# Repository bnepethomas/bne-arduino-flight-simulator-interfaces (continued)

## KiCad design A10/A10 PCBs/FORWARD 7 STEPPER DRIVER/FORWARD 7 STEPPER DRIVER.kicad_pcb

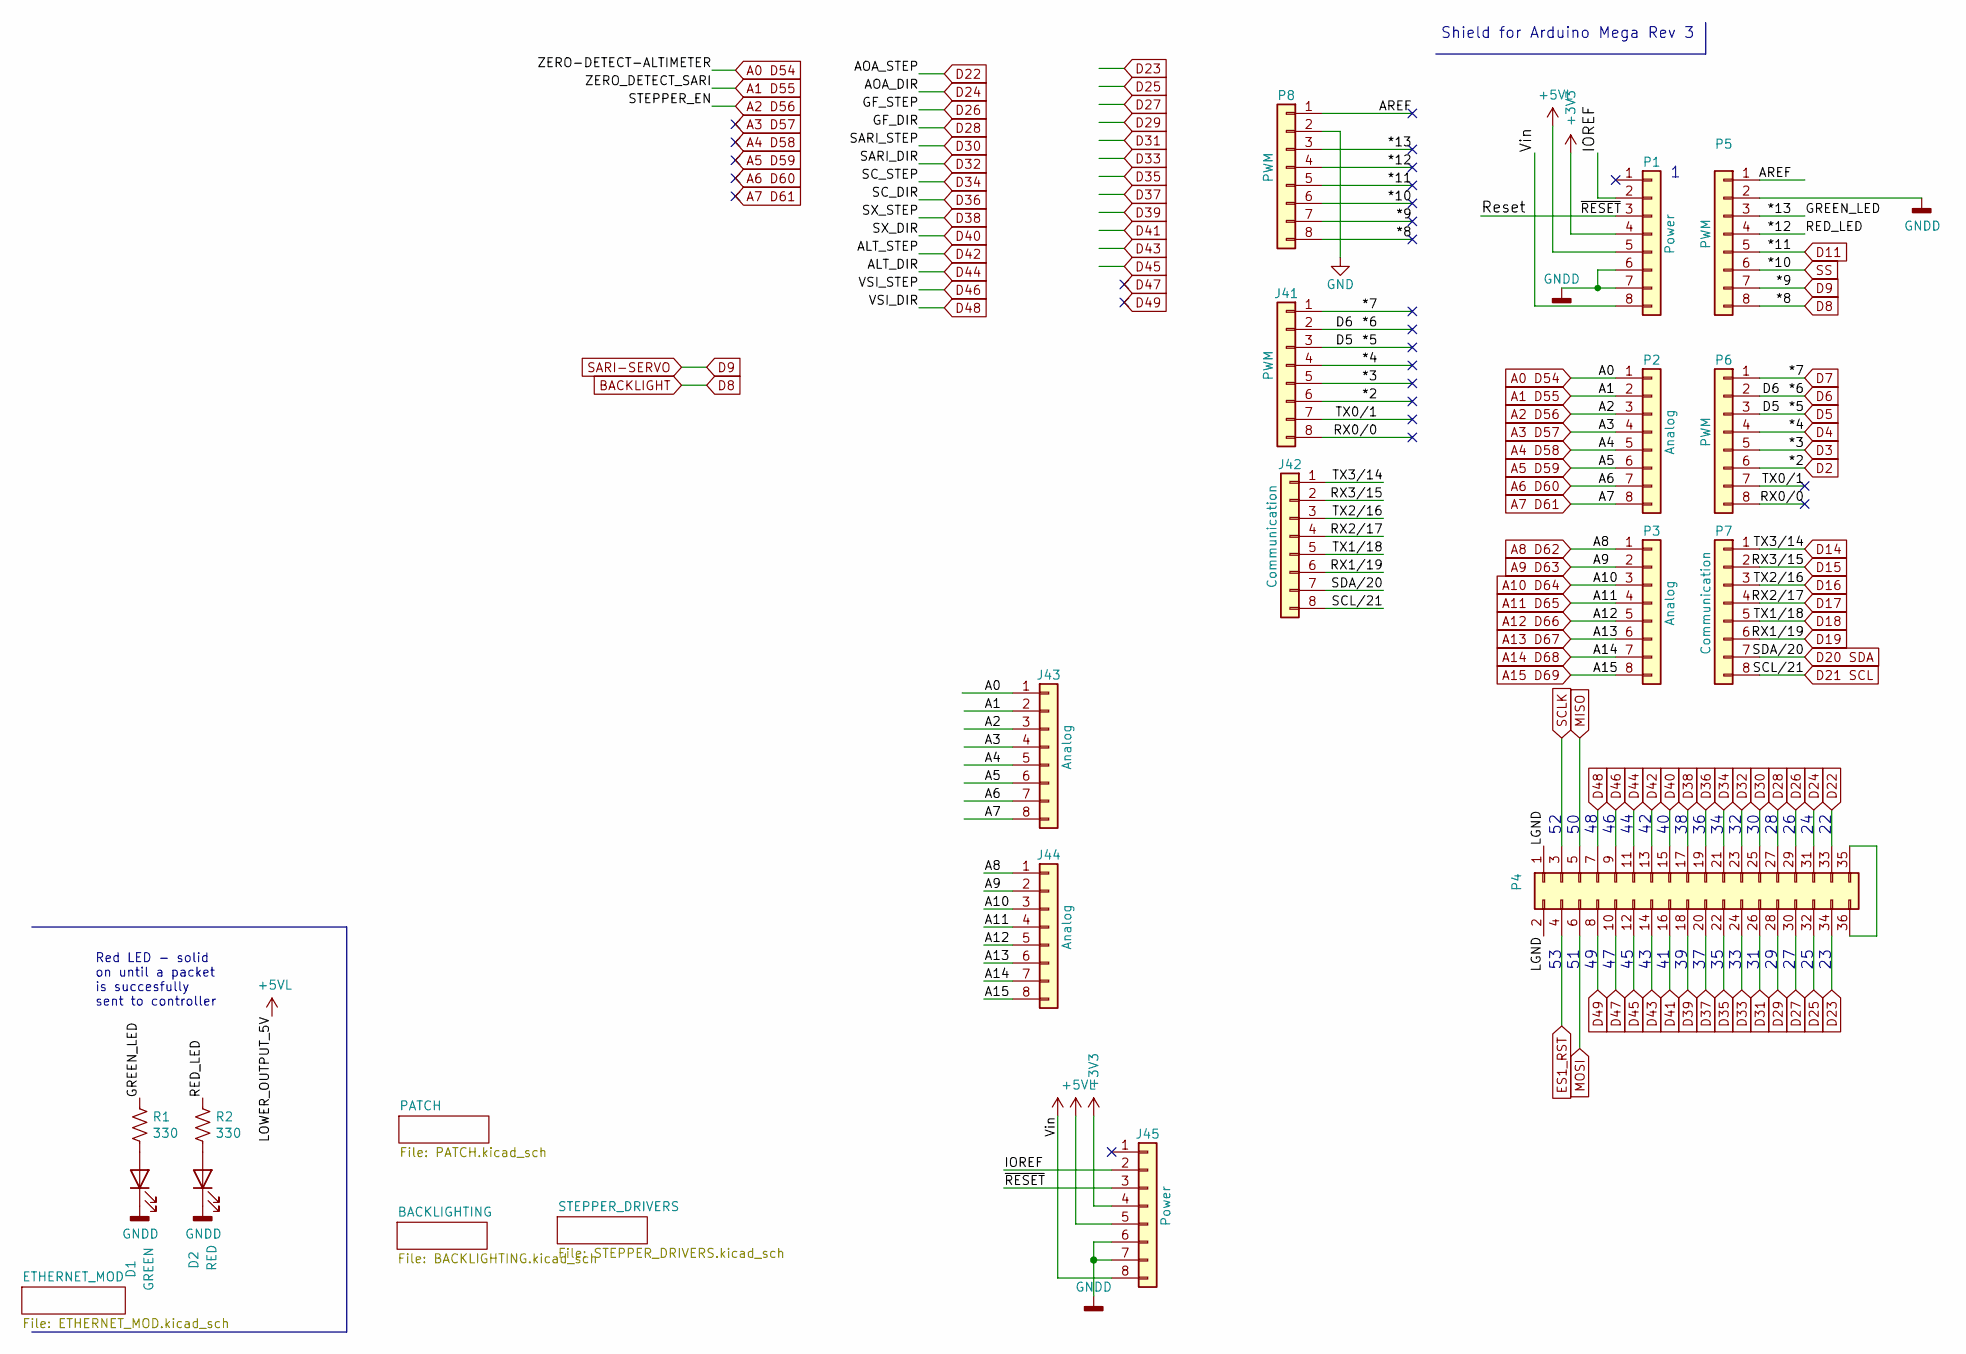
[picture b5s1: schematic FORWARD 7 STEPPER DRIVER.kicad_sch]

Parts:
D1: GREEN; LED_D3.0mm
D2: RED; LED_D3.0mm
J41: PWM; PinSocket_1x08_P2.54mm_Vertical
J42: Communication; PinSocket_1x08_P2.54mm_Vertical
J43, J44: Analog; PinSocket_1x08_P2.54mm_Vertical
J45: Power; PinSocket_1x08_P2.54mm_Vertical
P1: Power; Socket_Strip_Arduino_1x08
P2, P3: Analog; Socket_Strip_Arduino_1x08
P4: Digital; Socket_Strip_Arduino_2x18
P5, P6, P8: PWM; Socket_Strip_Arduino_1x08
P7: Communication; Socket_Strip_Arduino_1x08
R1: 330; R_Axial_DIN0204_L3.6mm_D1.6mm_P2.54mm_Vertical
R2: 330; PT_R_Axial_DIN0204_L3.6mm_D1.6mm_P2.54mm_Vertical

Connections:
+3V3: J45.4, P1.4; also elsewhere on the board
+5VL: J45.5, P1.5; also elsewhere on the board
/*12: P5.4, P8.4, R2.1
/*13: P5.3, P8.3, R1.1
/AREF: P5.1, P8.1
/IOREF: J45.2, P1.2
/LGND: P4.1, P4.2
/RX0/0: J41.8, P6.8
/Reset: J45.3, P1.3
/TX0/1: J41.7, P6.7
A0 D54: J43.1, P2.1; also elsewhere on the board
A1 D55: J43.2, P2.2; also elsewhere on the board
A2 D56: J43.3, P2.3; also elsewhere on the board
A3 D57: J43.4, P2.4
A4 D58: J43.5, P2.5
A5 D59: J43.6, P2.6
A6 D60: J43.7, P2.7
A7 D61: J43.8, P2.8
A8 D62: J44.1, P3.1
A9 D63: J44.2, P3.2
A10 D64: J44.3, P3.3
A11 D65: J44.4, P3.4
A12 D66: J44.5, P3.5
A13 D67: J44.6, P3.6
A14 D68: J44.7, P3.7
A15 D69: J44.8, P3.8
BACKLIGHT: P5.8, P8.8; also elsewhere on the board
D2: J41.6, P6.6
D3: J41.5, P6.5
D4: J41.4, P6.4
D5: J41.3, P6.3
D6: J41.2, P6.2
D7: J41.1, P6.1
D9: P5.7, P8.7; also elsewhere on the board
D11: P5.5, P8.5
D14: J42.1, P7.1
D15: J42.2, P7.2
D16: J42.3, P7.3
D17: J42.4, P7.4
D18: J42.5, P7.5
D19: J42.6, P7.6
D20 SDA: J42.7, P7.7
D21 SCL: J42.8, P7.8
D22: P4.33; also elsewhere on the board
D23: P4.34
D24: P4.31; also elsewhere on the board
D25: P4.32
D26: P4.29; also elsewhere on the board
D27: P4.30
D28: P4.27; also elsewhere on the board
D29: P4.28
D30: P4.25; also elsewhere on the board
D31: P4.26
D32: P4.23; also elsewhere on the board
D33: P4.24
D34: P4.21; also elsewhere on the board
D35: P4.22
D36: P4.19; also elsewhere on the board
D37: P4.20
D38: P4.17; also elsewhere on the board
D39: P4.18
D40: P4.15; also elsewhere on the board
D41: P4.16
D42: P4.13; also elsewhere on the board
D43: P4.14
D44: P4.11; also elsewhere on the board
D45: P4.12
D46: P4.9; also elsewhere on the board
D47: P4.10
D48: P4.7; also elsewhere on the board
D49: P4.8
ES1_RST: P4.4; also elsewhere on the board
GND: D1.1 (K), D2.1 (K), J45.6, J45.7, P1.6, P1.7, P5.2, P8.2; also elsewhere on the board
MISO: P4.5; also elsewhere on the board
MOSI: P4.6; also elsewhere on the board
unnamed: D1.2 (A), R1.2
unnamed: D2.2 (A), R2.2
unnamed: P4.35, P4.36
SCLK: P4.3; also elsewhere on the board
SS: P5.6, P8.6; also elsewhere on the board
VCC: J45.8, P1.8

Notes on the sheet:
Shield for Arduino Mega Rev 3
Red LED - solid on until a packet is succesfully sent to controller

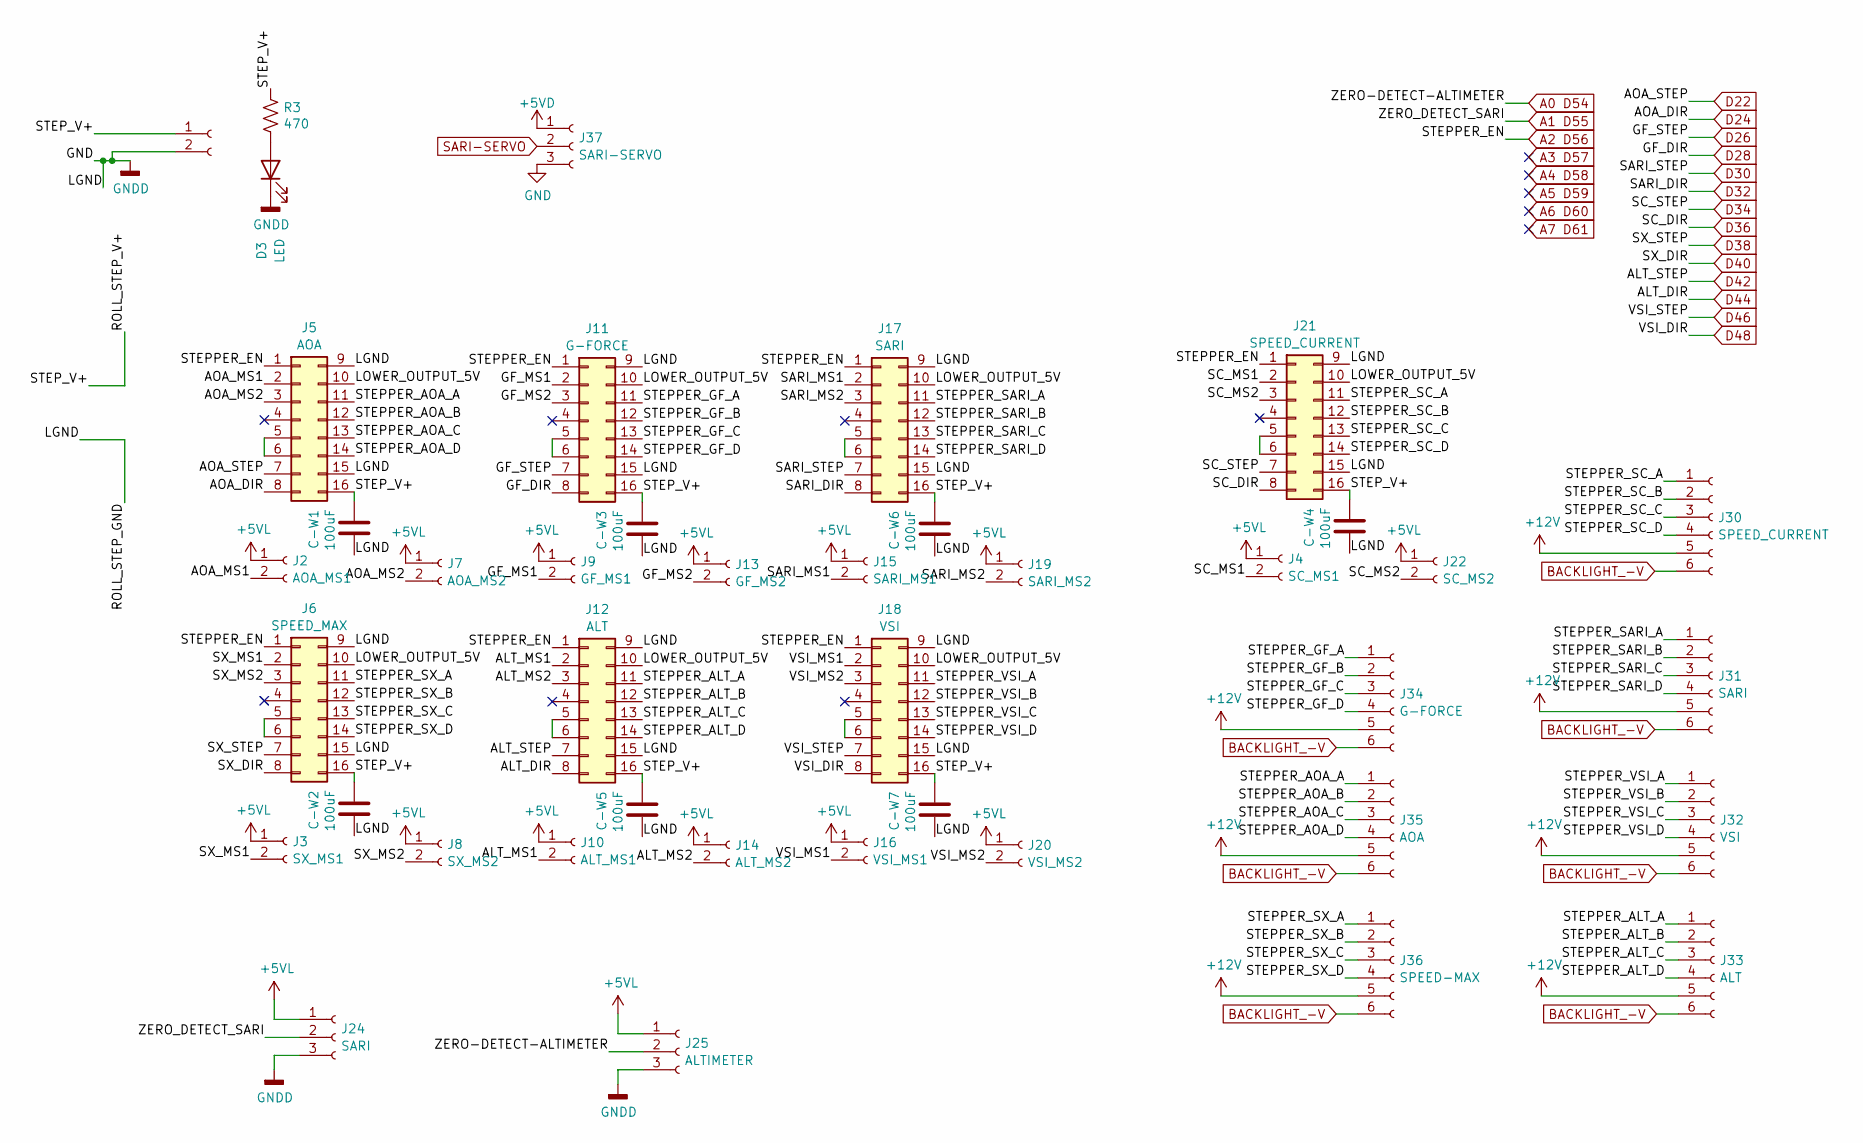
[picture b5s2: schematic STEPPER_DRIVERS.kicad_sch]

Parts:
C-W1, C-W2, C-W3, C-W4, C-W5, C-W6, C-W7: 100uF; C_Radial_D8.0mm_H7.0mm_P3.50mm
D3: LED; LED_D3.0mm
J1: STEPPER IN 12-20VDC; BarrelJack_Horizontal
J2: AOA_MS1; PinHeader_1x02_P2.54mm_Vertical
J3: SX_MS1; PinHeader_1x02_P2.54mm_Vertical
J4: SC_MS1; PinHeader_1x02_P2.54mm_Vertical
J5: AOA; Pololu_Breakout-16_15.2x20.3mm
J6: SPEED_MAX; Pololu_Breakout-16_15.2x20.3mm
J7: AOA_MS2; PinHeader_1x02_P2.54mm_Vertical
J8: SX_MS2; PinHeader_1x02_P2.54mm_Vertical
J9: GF_MS1; PinHeader_1x02_P2.54mm_Vertical
J10: ALT_MS1; PinHeader_1x02_P2.54mm_Vertical
J11: G-FORCE; Pololu_Breakout-16_15.2x20.3mm
J12: ALT; Pololu_Breakout-16_15.2x20.3mm
J13: GF_MS2; PinHeader_1x02_P2.54mm_Vertical
J14: ALT_MS2; PinHeader_1x02_P2.54mm_Vertical
J15: SARI_MS1; PinHeader_1x02_P2.54mm_Vertical
J16: VSI_MS1; PinHeader_1x02_P2.54mm_Vertical
J17: SARI; Pololu_Breakout-16_15.2x20.3mm
J18: VSI; Pololu_Breakout-16_15.2x20.3mm
J19: SARI_MS2; PinHeader_1x02_P2.54mm_Vertical
J20: VSI_MS2; PinHeader_1x02_P2.54mm_Vertical
J21: SPEED_CURRENT; Pololu_Breakout-16_15.2x20.3mm
J22: SC_MS2; PinHeader_1x02_P2.54mm_Vertical
J24: SARI; Molex_KK-254_AE-6410-03A_1x03_P2.54mm_Vertical
J25: ALTIMETER; Molex_KK-254_AE-6410-03A_1x03_P2.54mm_Vertical
J30: SPEED_CURRENT; Molex_KK-254_AE-6410-06A_1x06_P2.54mm_Vertical
J31: SARI; Molex_KK-254_AE-6410-06A_1x06_P2.54mm_Vertical
J32: VSI; Molex_KK-254_AE-6410-06A_1x06_P2.54mm_Vertical
J33: ALT; Molex_KK-254_AE-6410-06A_1x06_P2.54mm_Vertical
J34: G-FORCE; Molex_KK-254_AE-6410-06A_1x06_P2.54mm_Vertical
J35: AOA; Molex_KK-254_AE-6410-06A_1x06_P2.54mm_Vertical
J36: SPEED-MAX; Molex_KK-254_AE-6410-06A_1x06_P2.54mm_Vertical
J37: SARI-SERVO; Molex_KK-254_AE-6410-03A_1x03_P2.54mm_Vertical
R3: 470; R_Axial_DIN0204_L3.6mm_D1.6mm_P2.54mm_Vertical

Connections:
+5VL: J2.1, J3.1, J4.1, J7.1, J8.1, J9.1, J10.1, J13.1, J14.1, J15.1, J16.1, J19.1, J20.1, J22.1, J24.1, J25.1; also elsewhere on the board
+12V: J30.5, J31.5, J32.5, J33.5, J34.5, J35.5, J36.5; also elsewhere on the board
/STEPPER_DRIVERS/ALT_MS1: J10.2, J12.2
/STEPPER_DRIVERS/ALT_MS2: J12.3, J14.2
/STEPPER_DRIVERS/AOA_MS1: J2.2, J5.2
/STEPPER_DRIVERS/AOA_MS2: J5.3, J7.2
/STEPPER_DRIVERS/GF_MS1: J9.2, J11.2
/STEPPER_DRIVERS/GF_MS2: J11.3, J13.2
/STEPPER_DRIVERS/LOWER_OUTPUT_5V: J5.10, J6.10, J11.10, J12.10, J17.10, J18.10, J21.10
/STEPPER_DRIVERS/SARI_MS1: J15.2, J17.2
/STEPPER_DRIVERS/SARI_MS2: J17.3, J19.2
/STEPPER_DRIVERS/SC_MS1: J4.2, J21.2
/STEPPER_DRIVERS/SC_MS2: J21.3, J22.2
/STEPPER_DRIVERS/STEPPER_ALT_A: J12.11, J33.1
/STEPPER_DRIVERS/STEPPER_ALT_B: J12.12, J33.2
/STEPPER_DRIVERS/STEPPER_ALT_C: J12.13, J33.3
/STEPPER_DRIVERS/STEPPER_ALT_D: J12.14, J33.4
/STEPPER_DRIVERS/STEPPER_AOA_A: J5.11, J35.1
/STEPPER_DRIVERS/STEPPER_AOA_B: J5.12, J35.2
/STEPPER_DRIVERS/STEPPER_AOA_C: J5.13, J35.3
/STEPPER_DRIVERS/STEPPER_AOA_D: J5.14, J35.4
/STEPPER_DRIVERS/STEPPER_GF_A: J11.11, J34.1
/STEPPER_DRIVERS/STEPPER_GF_B: J11.12, J34.2
/STEPPER_DRIVERS/STEPPER_GF_C: J11.13, J34.3
/STEPPER_DRIVERS/STEPPER_GF_D: J11.14, J34.4
/STEPPER_DRIVERS/STEPPER_SARI_A: J17.11, J31.1
/STEPPER_DRIVERS/STEPPER_SARI_B: J17.12, J31.2
/STEPPER_DRIVERS/STEPPER_SARI_C: J17.13, J31.3
/STEPPER_DRIVERS/STEPPER_SARI_D: J17.14, J31.4
/STEPPER_DRIVERS/STEPPER_SC_A: J21.11, J30.1
/STEPPER_DRIVERS/STEPPER_SC_B: J21.12, J30.2
/STEPPER_DRIVERS/STEPPER_SC_C: J21.13, J30.3
/STEPPER_DRIVERS/STEPPER_SC_D: J21.14, J30.4
/STEPPER_DRIVERS/STEPPER_SX_A: J6.11, J36.1
/STEPPER_DRIVERS/STEPPER_SX_B: J6.12, J36.2
/STEPPER_DRIVERS/STEPPER_SX_C: J6.13, J36.3
/STEPPER_DRIVERS/STEPPER_SX_D: J6.14, J36.4
/STEPPER_DRIVERS/STEPPER_VSI_A: J18.11, J32.1
/STEPPER_DRIVERS/STEPPER_VSI_B: J18.12, J32.2
/STEPPER_DRIVERS/STEPPER_VSI_C: J18.13, J32.3
/STEPPER_DRIVERS/STEPPER_VSI_D: J18.14, J32.4
/STEPPER_DRIVERS/SX_MS1: J3.2, J6.2
/STEPPER_DRIVERS/SX_MS2: J6.3, J8.2
/STEPPER_DRIVERS/VSI_MS1: J16.2, J18.2
/STEPPER_DRIVERS/VSI_MS2: J18.3, J20.2
A0 D54: J25.2; also elsewhere on the board
A1 D55: J24.2; also elsewhere on the board
A2 D56: J5.1, J6.1, J11.1, J12.1, J17.1, J18.1, J21.1; also elsewhere on the board
BACKLIGHT_-V: J30.6, J31.6, J32.6, J33.6, J34.6, J35.6, J36.6; also elsewhere on the board
D9: J37.2; also elsewhere on the board
D22: J5.7; also elsewhere on the board
D24: J5.8; also elsewhere on the board
D26: J11.7; also elsewhere on the board
D28: J11.8; also elsewhere on the board
D30: J17.7; also elsewhere on the board
D32: J17.8; also elsewhere on the board
D34: J21.7; also elsewhere on the board
D36: J21.8; also elsewhere on the board
D38: J6.7; also elsewhere on the board
D40: J6.8; also elsewhere on the board
D42: J12.7; also elsewhere on the board
D44: J12.8; also elsewhere on the board
D46: J18.7; also elsewhere on the board
D48: J18.8; also elsewhere on the board
GND: C-W1.2, C-W2.2, C-W3.2, C-W4.2, C-W5.2, C-W6.2, C-W7.2, D3.1 (K), J1.2, J5.9, J5.15, J6.9, J6.15, J11.9, J11.15, J12.9, J12.15, J17.9, J17.15, J18.9, J18.15, J21.9, J21.15, J24.3, J25.3, J37.3; also elsewhere on the board
unnamed: D3.2 (A), R3.2
unnamed: J5.5, J5.6
unnamed: J6.5, J6.6
unnamed: J11.5, J11.6
unnamed: J12.5, J12.6
unnamed: J17.5, J17.6
unnamed: J18.5, J18.6
unnamed: J21.5, J21.6

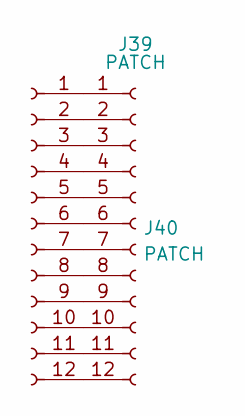
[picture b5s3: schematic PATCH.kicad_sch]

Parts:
J39, J40: PATCH; PinSocket_1x12_P2.54mm_Vertical

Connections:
unnamed: J39.1, J40.1
unnamed: J39.2, J40.2
unnamed: J39.3, J40.3
unnamed: J39.4, J40.4
unnamed: J39.5, J40.5
unnamed: J39.6, J40.6
unnamed: J39.7, J40.7
unnamed: J39.8, J40.8
unnamed: J39.9, J40.9
unnamed: J39.10, J40.10
unnamed: J39.11, J40.11
unnamed: J39.12, J40.12

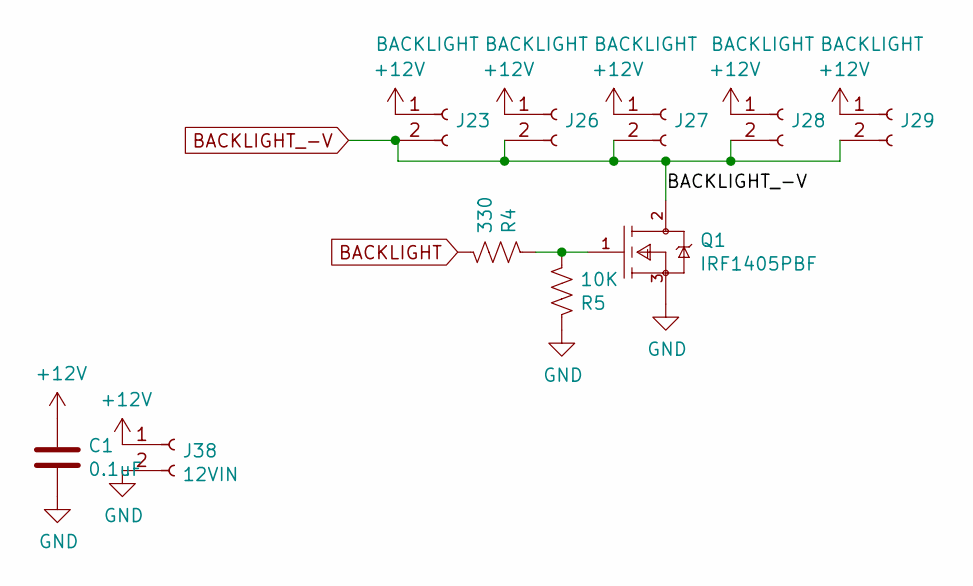
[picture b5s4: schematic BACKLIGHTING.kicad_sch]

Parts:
C1: 0.1uF; C_Disc_D4.3mm_W1.9mm_P5.00mm
J23, J26, J27, J28, J29: BACKLIGHT; Molex_KK-254_AE-6410-02A_1x02_P2.54mm_Vertical
J38: 12VIN; BarrelJack_Horizontal
Q1: IRF1405PBF; TO-220-3_Vertical; mouser part number 942-IRF1405PBF; digikey description MOSFET N-CH 55V 169A TO-220AB
R4: 330; R_Axial_DIN0204_L3.6mm_D1.6mm_P2.54mm_Vertical
R5: 10K; R_Axial_DIN0204_L3.6mm_D1.6mm_P2.54mm_Vertical

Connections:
+12V: C1.1, J23.1, J26.1, J27.1, J28.1, J29.1, J38.1; also elsewhere on the board
BACKLIGHT: R4.2; also elsewhere on the board
BACKLIGHT_-V: J23.2, J26.2, J27.2, J28.2, J29.2, Q1.2 (D); also elsewhere on the board
GND: C1.2, J38.2, Q1.3 (S), R5.1; also elsewhere on the board
unnamed: Q1.1 (G), R4.1, R5.2

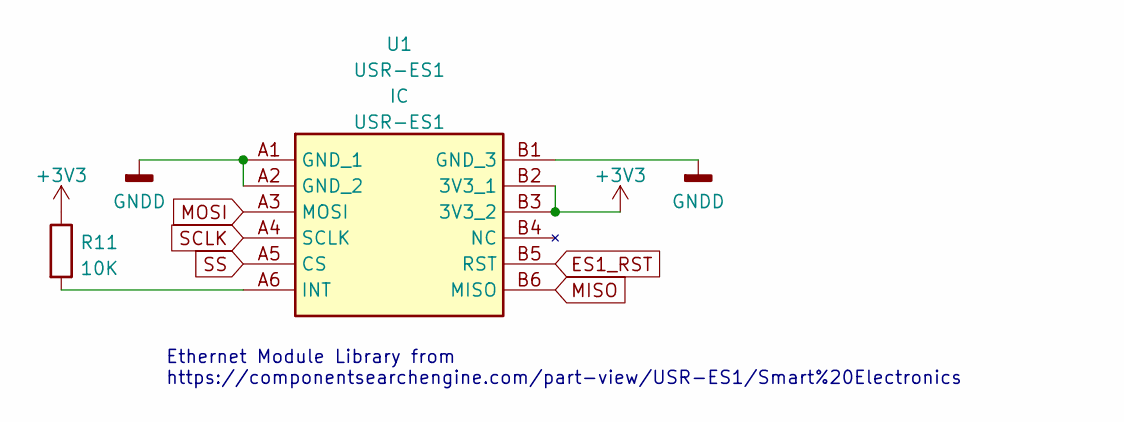
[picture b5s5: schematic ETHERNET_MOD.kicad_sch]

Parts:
R11: 10K; PT_R_Axial_DIN0204_L3.6mm_D1.6mm_P2.54mm_Vertical
U1: USR-ES1; USRES1; Manufacturer_Part_Number USR-ES1

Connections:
+3V3: R11.1, U1.B2 (3V3_1), U1.B3 (3V3_2); also elsewhere on the board
ES1_RST: U1.B5 (RST); also elsewhere on the board
GND: U1.A1 (GND_1), U1.A2 (GND_2), U1.B1 (GND_3); also elsewhere on the board
MISO: U1.B6 (MISO); also elsewhere on the board
MOSI: U1.A3 (MOSI); also elsewhere on the board
unnamed: R11.2, U1.A6 (INT)
SCLK: U1.A4 (SCLK); also elsewhere on the board
SS: U1.A5 (CS); also elsewhere on the board

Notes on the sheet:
Ethernet Module Library from https://componentsearchengine.com/part-view/USR-ES1/Smart%20Electronics

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
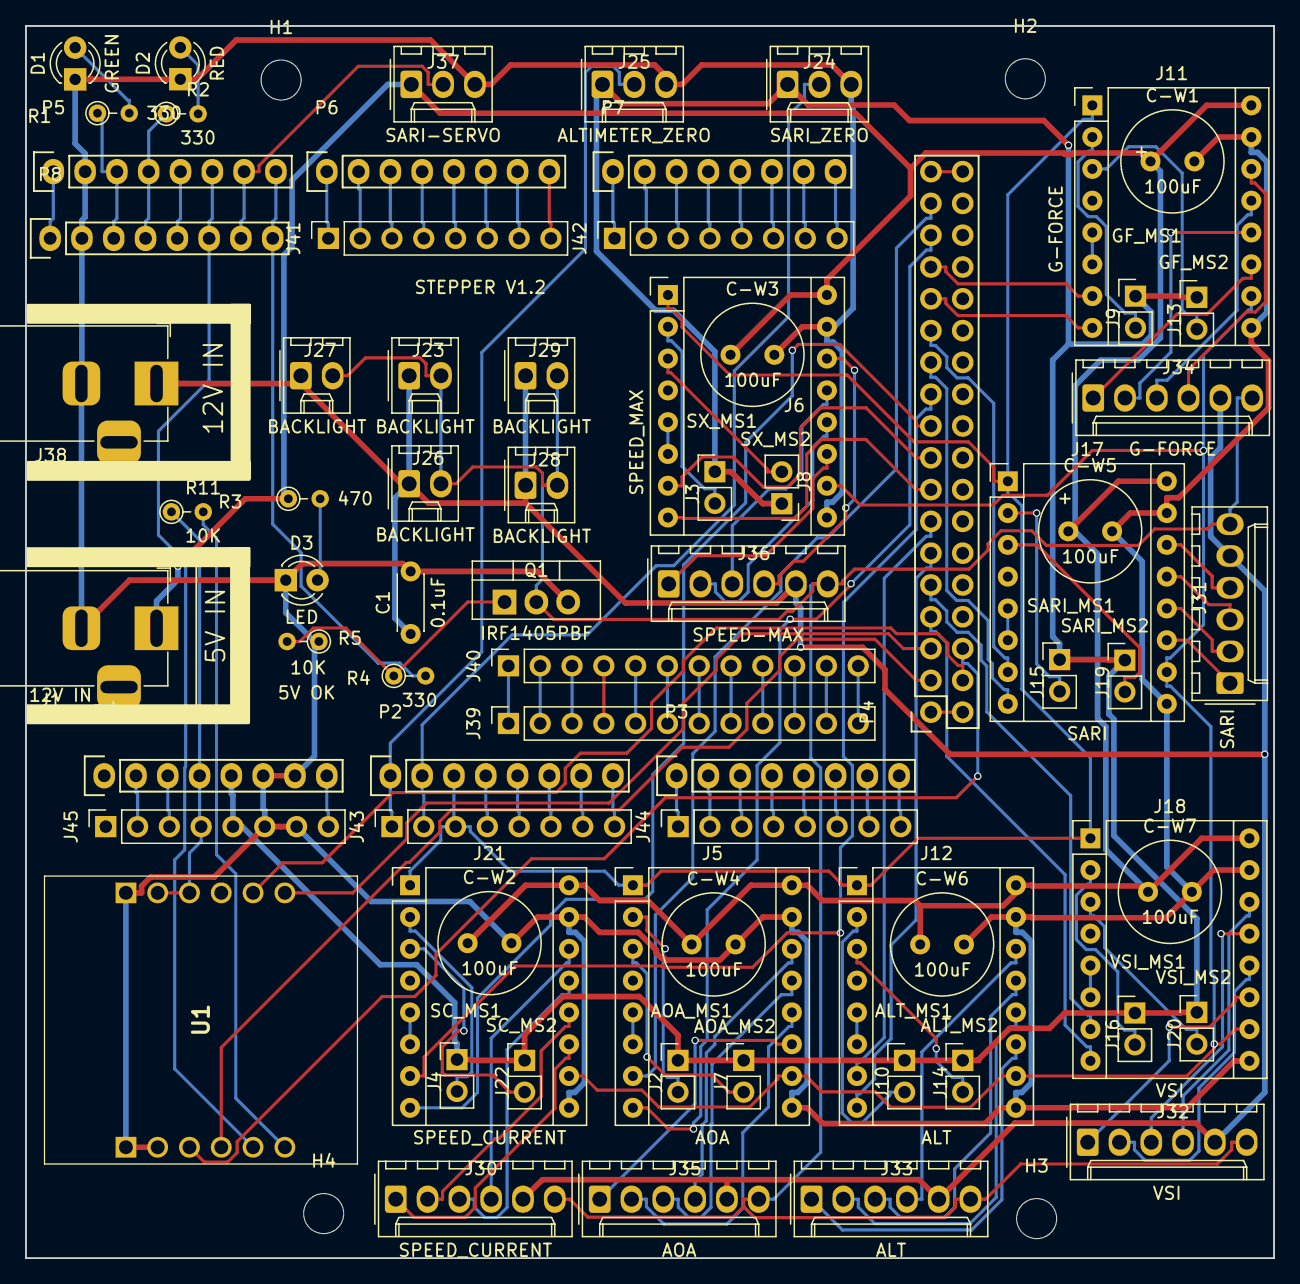
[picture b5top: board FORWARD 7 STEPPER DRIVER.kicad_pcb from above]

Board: 2 copper layers, 99.7 x 98.4 mm, 76 parts (0 on the bottom side), 135 nets.

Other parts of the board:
H1, H2, H3, H4: MountingHole; MountingHole_3.2mm_M3

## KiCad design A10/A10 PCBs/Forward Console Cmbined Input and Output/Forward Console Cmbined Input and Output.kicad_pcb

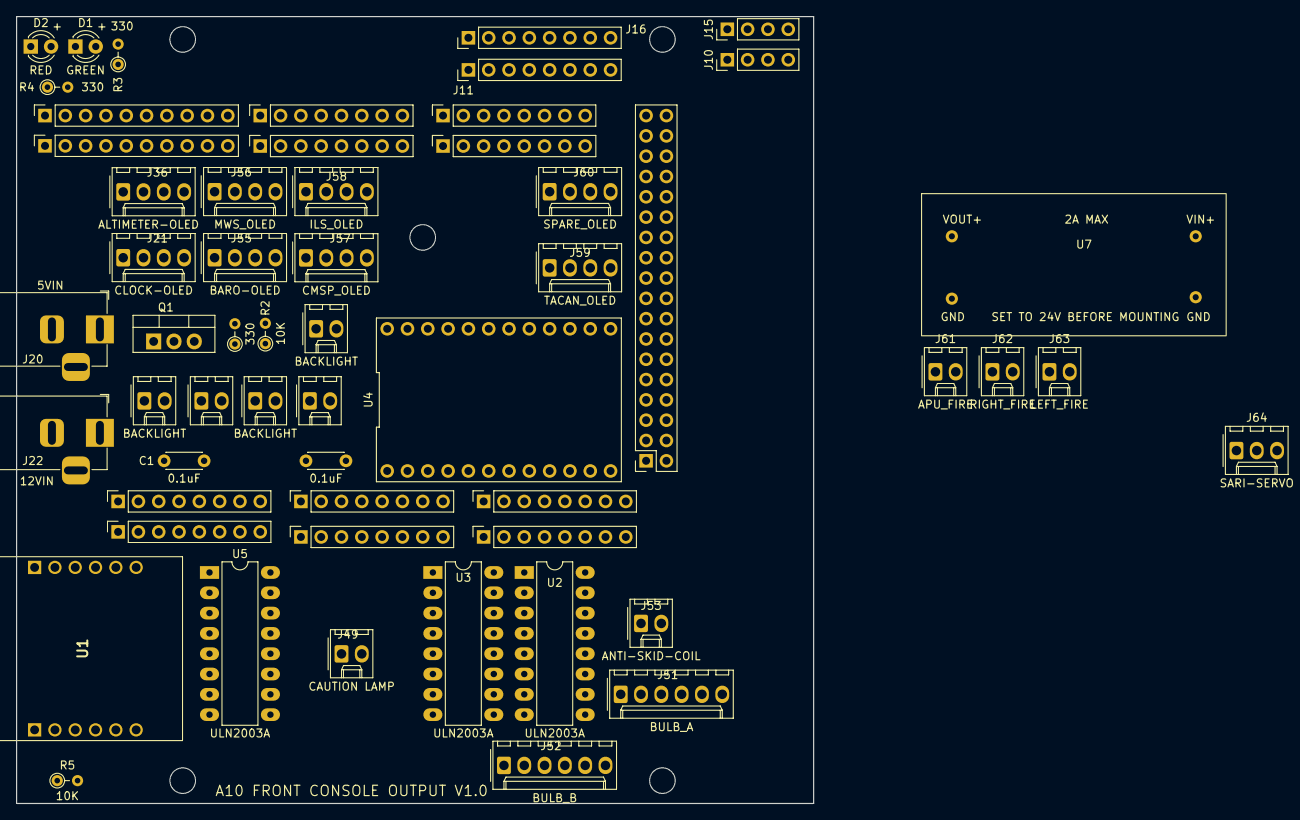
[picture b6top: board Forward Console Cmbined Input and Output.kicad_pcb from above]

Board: 2 copper layers, 99.7 x 98.4 mm, 61 parts (0 on the bottom side), 100 nets, no tracks yet.

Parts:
C1, C2: 0.1uF; C_Disc_D4.3mm_W1.9mm_P5.00mm
D1: GREEN; LED_D3.0mm
D2: RED; LED_D3.0mm
H1, H2, H3, H4: MountingHole; MountingHole_3.2mm
J3, J6, J9, J14, J19: BACKLIGHT; Molex_KK-254_AE-6410-02A_1x02_P2.54mm_Vertical
J10, J15: PATCH; PinHeader_1x04_P2.54mm_Vertical
J11, J16: PATCH; PinHeader_1x08_P2.54mm_Vertical
J20: 5VIN; BarrelJack_Horizontal
J21: CLOCK-OLED; Molex_KK-254_AE-6410-04A_1x04_P2.54mm_Vertical
J22: 12VIN; BarrelJack_Horizontal
J24, J46: PWM; PinSocket_1x10_P2.54mm_Vertical
J25, J47: PWM; PinSocket_1x08_P2.54mm_Vertical
J26, J48: Communication; PinSocket_1x08_P2.54mm_Vertical
J32, J33, J43, J44: Analog; PinSocket_1x08_P2.54mm_Vertical
J36: ALTIMETER-OLED; Molex_KK-254_AE-6410-04A_1x04_P2.54mm_Vertical
J41, J42: Power; PinSocket_1x08_P2.54mm_Vertical
J45: Digital; PinSocket_2x18_P2.54mm_Vertical
J49: CAUTION LAMP; Molex_KK-254_AE-6410-02A_1x02_P2.54mm_Vertical
J51: BULB_A; Molex_KK-254_AE-6410-06A_1x06_P2.54mm_Vertical
J52: BULB_B; Molex_KK-254_AE-6410-06A_1x06_P2.54mm_Vertical
J53: ANTI-SKID-COIL; Molex_KK-254_AE-6410-02A_1x02_P2.54mm_Vertical
J55: BARO-OLED; Molex_KK-254_AE-6410-04A_1x04_P2.54mm_Vertical
J56: MWS_OLED; Molex_KK-254_AE-6410-04A_1x04_P2.54mm_Vertical
J57: CMSP_OLED; Molex_KK-254_AE-6410-04A_1x04_P2.54mm_Vertical
J58: ILS_OLED; Molex_KK-254_AE-6410-04A_1x04_P2.54mm_Vertical
J59: TACAN_OLED; Molex_KK-254_AE-6410-04A_1x04_P2.54mm_Vertical
J60: SPARE_OLED; Molex_KK-254_AE-6410-04A_1x04_P2.54mm_Vertical
J61: APU_FIRE; Molex_KK-254_AE-6410-02A_1x02_P2.54mm_Vertical
J62: RIGHT_FIRE; Molex_KK-254_AE-6410-02A_1x02_P2.54mm_Vertical
J63: LEFT_FIRE; Molex_KK-254_AE-6410-02A_1x02_P2.54mm_Vertical
J64: SARI-SERVO; Molex_KK-254_AE-6410-03A_1x03_P2.54mm_Vertical
MH1: MountingHole_3.2mm
Q1: IRF1405PBF; TO-220-3_Vertical
R1, R3, R4: 330; R_Axial_DIN0204_L3.6mm_D1.6mm_P2.54mm_Vertical
R2, R5: 10K; R_Axial_DIN0204_L3.6mm_D1.6mm_P2.54mm_Vertical
U1: USR-ES1; USRES1
U2, U3, U5: ULN2003A; DIP-16_W7.62mm_LongPads
U4: TCA9548APWR; DIP-24_TCA9548A
U7: VIRIABLE BUCK; VARIABLE_BUCK

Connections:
+3V3: J41.4, J42.4, R5.1, U1.B2 (3V3_1), U1.B3 (3V3_2), U4.1 (VCC)
+5V: J21.1, J36.1, J41.5, J42.5, J45.35, J45.36, J55.1, J56.1, J57.1, J58.1, J59.1, J60.1
+5VD: C1.1, J20.1, J64.1
+12V: C2.1, J3.1, J6.1, J9.1, J14.1, J19.1, J22.1, J49.1, J51.1, J52.1, J53.1, U2.9 (COM), U3.9 (COM), U7.1 (VIN)
+24V: J61.1, J62.1, J63.1, U5.9 (COM), U7.4 (24V_OUT)
/*12: J24.6, J46.6, R4.1
/*13: J24.5, J46.5, R3.1
/AREF: J24.3, J46.3
/COIL AND LAMP DRIVERS/ANCHR: J52.4, U3.15 (O2)
/COIL AND LAMP DRIVERS/B_APU_FIRE: J61.2, U5.15 (O2)
/COIL AND LAMP DRIVERS/B_LEFT_FIRE: J63.2, U5.16 (O1)
/COIL AND LAMP DRIVERS/B_RIGHT_FIRE: J62.2, U5.14 (O3)
/COIL AND LAMP DRIVERS/CAUTION_LAMP-: J49.2, U2.16 (O1)
/COIL AND LAMP DRIVERS/COIL_ANTI_SKID: J53.2, U3.12 (O5)
/COIL AND LAMP DRIVERS/EGI: J51.6, U2.11 (O6)
/COIL AND LAMP DRIVERS/HARS: J51.5, U2.12 (O5)
/COIL AND LAMP DRIVERS/ILS: J52.6, U3.13 (O4)
/COIL AND LAMP DRIVERS/MISSLE LAUNCH: J51.4, U2.13 (O4)
/COIL AND LAMP DRIVERS/PRI: J51.2, U2.15 (O2)
/COIL AND LAMP DRIVERS/SEP: J51.3, U2.14 (O3)
/COIL AND LAMP DRIVERS/STR PT: J52.3, U3.16 (O1)
/COIL AND LAMP DRIVERS/TCN: J52.5, U3.14 (O3)
/COIL AND LAMP DRIVERS/TISL: J52.2, U2.10 (O7)
/IOREF: J41.2, J42.2
/OLED/SC0: J21.3, U4.10 (SC0)
/OLED/SC1: J36.3, U4.12 (SC1)
/OLED/SC2: J55.3, U4.14 (SC2)
/OLED/SC3: J56.3, U4.16 (SC3)
/OLED/SC4: J57.3, U4.18 (SC4)
/OLED/SC5: J58.3, U4.20 (SC5)
/OLED/SC6: J59.3, U4.22 (SC6)
/OLED/SC7: J60.3, U4.24 (SC7)
/OLED/SD0: J21.4, U4.9 (SD0)
/OLED/SD1: J36.4, U4.11 (SD1)
/OLED/SD2: J55.4, U4.13 (SD2)
/OLED/SD3: J56.4, U4.15 (SD3)
/OLED/SD4: J57.4, U4.17 (SD4)
/OLED/SD5: J58.4, U4.19 (SD5)
/OLED/SD6: J59.4, U4.21 (SD6)
/OLED/SD7: J60.4, U4.23 (SD7)
/RX0/0: J25.8, J47.8
/TX0/1: J25.7, J47.7
/~RESET: J41.3, J42.3
A0 D54: J32.1, J43.1, U5.1 (I1)
A1 D55: J32.2, J43.2, U5.2 (I2)
A2 D56: J32.3, J43.3, U5.3 (I3)
A3 D57: J32.4, J43.4
A4 D58: J32.5, J43.5, U2.1 (I1)
A5 D59: J32.6, J43.6, U2.2 (I2)
A6 D60: J32.7, J43.7, U2.3 (I3)
A7 D61: J32.8, J43.8, U2.4 (I4)
A8 D62: J33.1, J44.1, U2.5 (I5)
A9 D63: J33.2, J44.2, U2.6 (I6)
A10 D64: J33.3, J44.3, U2.7 (I7)
A11 D65: J33.4, J44.4, U3.1 (I1)
A12 D66: J33.5, J44.5, U3.2 (I2)
A13 D67: J33.6, J44.6, U3.3 (I3)
A14 D68: J33.7, J44.7, U3.4 (I4)
A15 D69: J33.8, J44.8, U3.5 (I5)
BACKLIGHT: J25.6, J47.6, R1.2
BACKLIGHT_-V: J3.2, J6.2, J9.2, J14.2, J19.2, Q1.2 (D)
D3: J25.5, J47.5
D4: J25.4, J47.4
D5: J25.3, J47.3
D6: J25.2, J47.2
D7: J25.1, J47.1
D8: J24.10, J46.10
D9: J24.9, J46.9
D11: J24.7, J46.7
D14: J26.1, J48.1, J64.2
D15: J26.2, J48.2
D16: J26.3, J48.3, U4.5 (~RESET)
D17: J26.4, J48.4, U4.8 (A2)
D18: J26.5, J48.5, U4.7 (A1)
D19: J26.6, J48.6, U4.6 (A0)
D20 SDA: J24.2, J26.7, J46.2, J48.7, U4.3 (SDA)
D21 SCL: J24.1, J26.8, J46.1, J48.8, U4.4 (SCL)
ES1_RST: J45.4, U1.B5 (RST)
GND: C1.2, C2.2, D1.1 (K), D2.1 (K), J20.2, J21.2, J22.2, J24.4, J36.2, J41.6, J41.7, J42.6, J42.7, J45.1, J45.2, J46.4, J55.2, J56.2, J57.2, J58.2, J59.2, J60.2, J64.3, Q1.3 (S), R2.1, U1.A1 (GND_1), U1.A2 (GND_2), U1.B1 (GND_3), U2.8 (GND), U3.6 (I6), U3.7 (I7), U3.8 (GND), U4.2 (GND), U5.6 (I6), U5.7 (I7), U5.8 (GND), U7.2 (GND), U7.3 (GND)
MISO: J45.5, U1.B6 (MISO)
MOSI: J45.6, U1.A3 (MOSI)
unnamed: D1.2 (A), R3.2
unnamed: D2.2 (A), R4.2
unnamed: J10.1, J15.1
unnamed: J10.2, J15.2
unnamed: J10.3, J15.3
unnamed: J10.4, J15.4
unnamed: J11.1, J16.1
unnamed: J11.2, J16.2
unnamed: J11.3, J16.3
unnamed: J11.4, J16.4
unnamed: J11.5, J16.5
unnamed: J11.6, J16.6
unnamed: J11.7, J16.7
unnamed: J11.8, J16.8
unnamed: Q1.1 (G), R1.1, R2.2
unnamed: R5.2, U1.A6 (INT)
SCLK: J45.3, U1.A4 (SCLK)
SS: J24.8, J46.8, U1.A5 (CS)
VCC: J41.8, J42.8
